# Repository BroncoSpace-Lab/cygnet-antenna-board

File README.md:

# antenna-board

This repo contains the KiCAD files for the PROVES Kit Antenna Board. This board currently goes on the +Z endcap of the satellite and hosts the antennas, interfacing ports, and some other support circuitry!

## antenna_top_cap_board_v1a
This antenna board is a reformat of the V1 Antenna Board that consolidates a bunch of the 2pos Picolock and STEMMA connectors into a single connector that runs back to the V3b EPS Board. We are probably going to leapfrog this version to land on V2 which fundementally changes things about the antenna feed path. 

## antenna_top_cap_v2
This version of the antenna top cap featuers major changes to the antenna feed path and debug passthroughs. Notable features are as follows: 
- Updated Balun Part Number (no longer sucks! still sucks to solder though)
- Addition of 12-pos and 5-pos Battery Board and Flight Controller Board debug connectors.

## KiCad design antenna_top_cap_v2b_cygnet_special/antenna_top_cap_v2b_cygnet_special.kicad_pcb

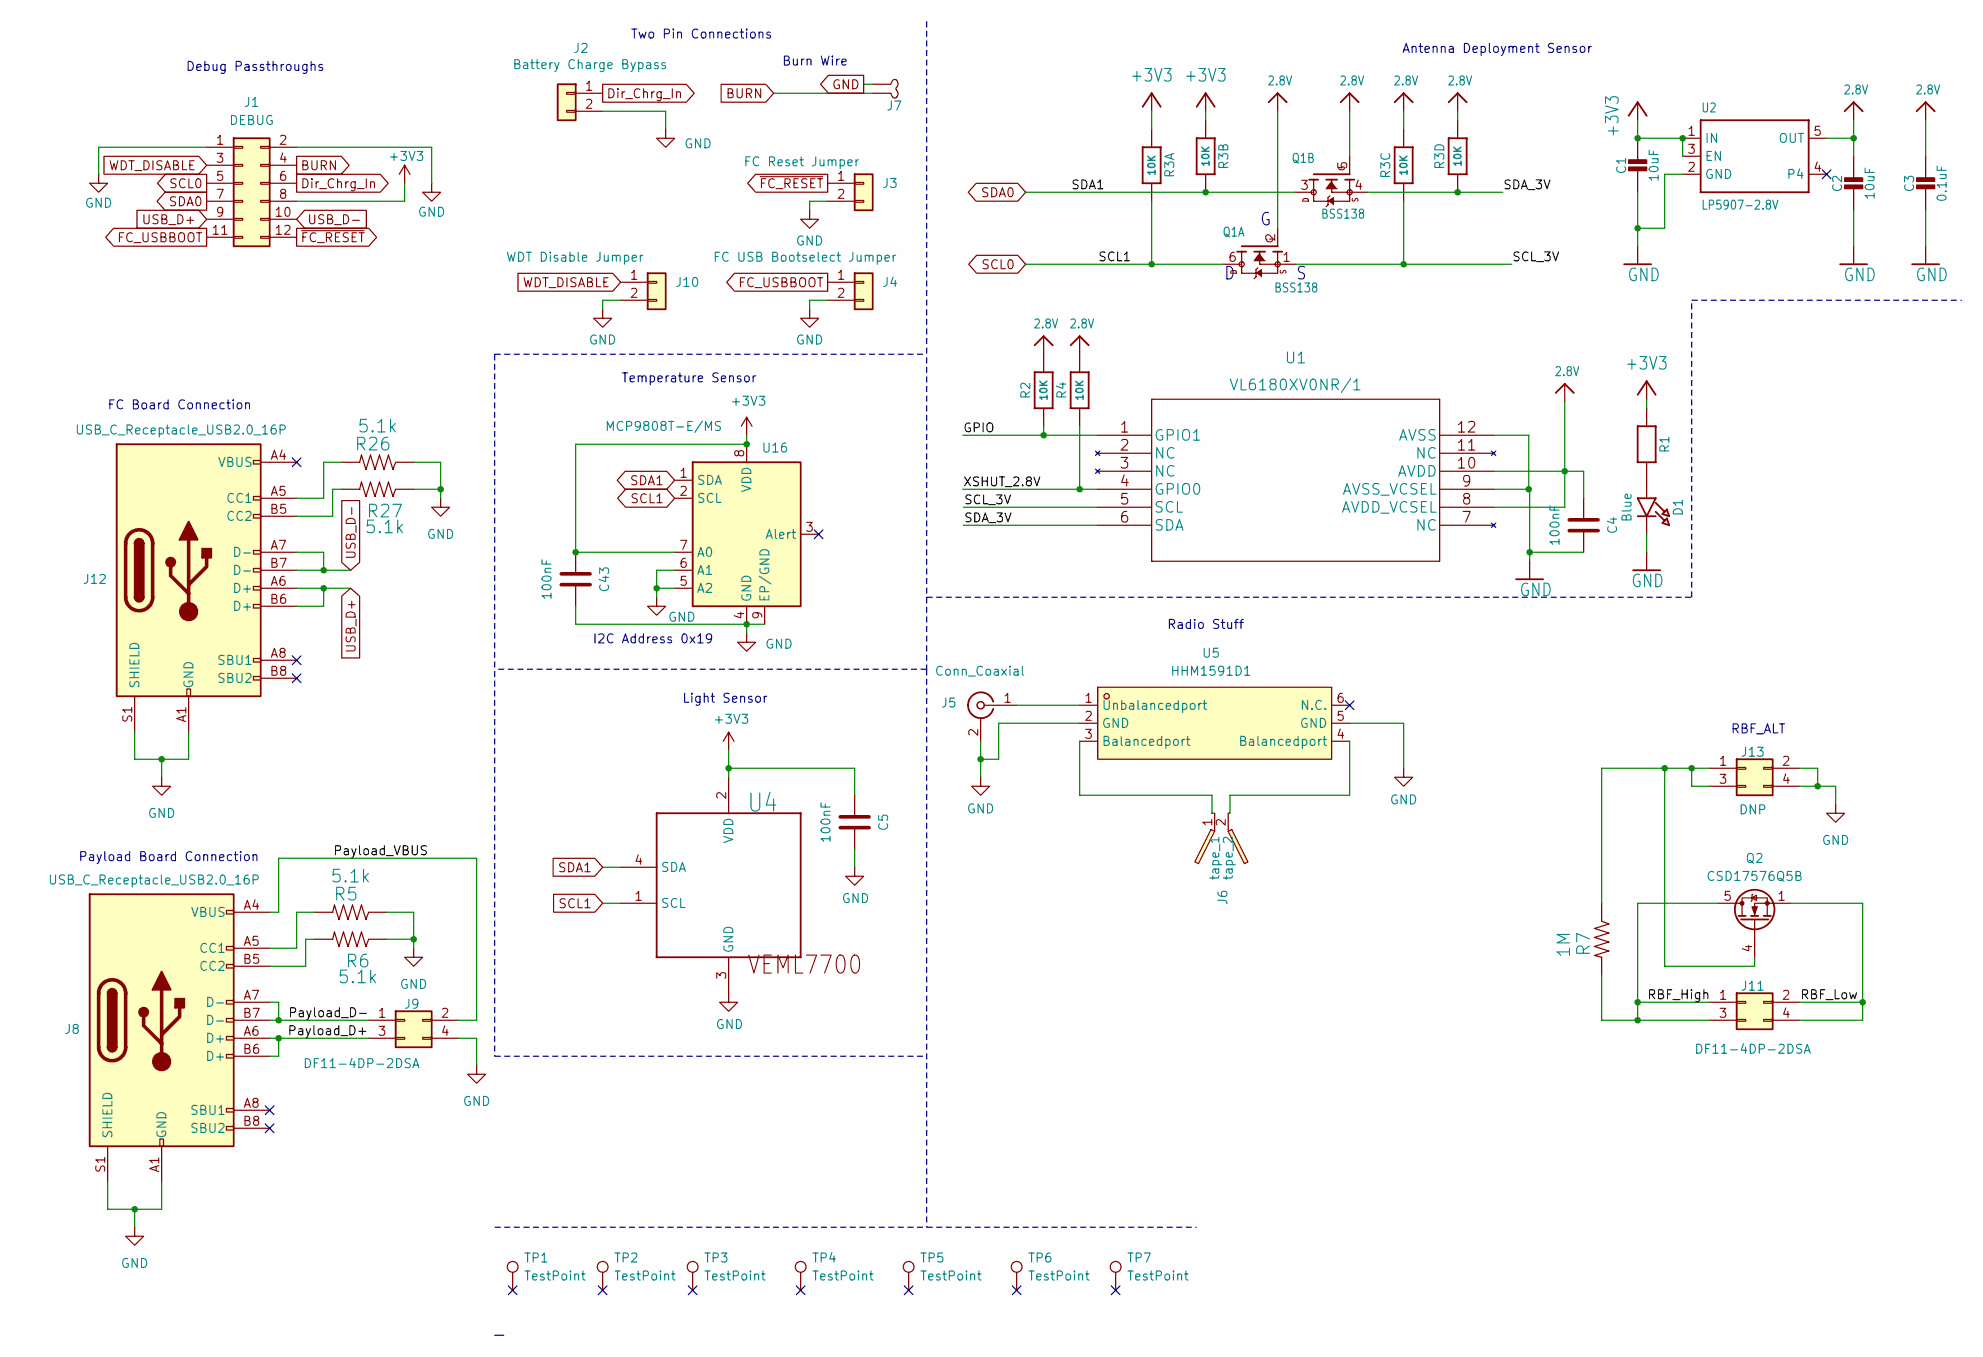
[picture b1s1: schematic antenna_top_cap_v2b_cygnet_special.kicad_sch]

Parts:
C1, C2: 10uF; C_0805_2012Metric
C3: 0.1uF; C_0603_1608Metric
C4, C5, C43: 100nF; C_0805_2012Metric
D1: Blue; LED_0603_1608Metric
J1: DEBUG; Hirose_DF11-12DP-2DSA_2x06_P2.00mm_Vertical
J2: Battery Charge Bypass; PinHeader_1x02_P2.54mm_Vertical
J3: FC Reset Jumper; PinHeader_1x02_P2.54mm_Vertical
J4: FC USB Bootselect Jumper; PinHeader_1x02_P2.54mm_Vertical
J5: Conn_Coaxial; SMA_Amphenol_901-144_Vertical
J6: Tape_Measure_Antenna
J7: Burn_Wire
J8, J12: USB_C_Receptacle_USB2.0_16P; USB_C_Receptacle_HRO_TYPE-C-31-M-12
J9, J11: DF11-4DP-2DSA; Hirose_DF11-4DP-2DSA_2x02_P2.00mm_Vertical
J10: WDT Disable Jumper; PinHeader_1x02_P2.54mm_Vertical
J13: DNP; Hirose_DF11-4DP-2DSA_2x02_P2.00mm_Vertical
Q1: BSS138; SOT-363_SC-70-6
Q2: CSD17576Q5B; TDSON-8-1
R1: 10k; R_0402_1005Metric
R2, R4: 10K; R_0603_1608Metric
R3: 10K; R_Array_Convex_4x0603
R5, R6, R26, R27: 5.1k; R_0603_1608Metric
R7: 1M; R_0603_1608Metric
TP1, TP2, TP3, TP4, TP5, TP6, TP7: TestPoint; MountingHole_2.7mm_M2.5_Pad
U1: VL6180XV0NR/1; VL6180
U2: LP5907-2.8V; SOT-23-5
U4: VEML7700; XDCR_VEML7700-TT
U5: HHM1591D1; XFMR-SMD_HHM1591D1; LCSC Part C74209
U16: MCP9808T-E/MS; MSOP-8-1EP_3x3mm_P0.65mm_EP1.5x1.8mm_ThermalVias

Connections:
2.8V: C2.1, C3.1, C4.1, Q1.2 (G), Q1.5 (G), R2.2, R3.3 (1), R3.4 (1), R4.2, U1.8 (AVDD_VCSEL), U1.10 (AVDD), U2.5 (OUT)
+3V3: C1.1, C5.1, C43.1, J1.8, R1.1, R3.1, R3.2 (1), U2.1 (IN), U2.3 (EN), U4.2 (VDD), U16.7 (A0), U16.8 (VDD)
/GPIO: R2.1, U1.1 (GPIO1)
/Payload_D+: J8.A6 (D+), J8.B6 (D+), J9.3
/Payload_D-: J8.A7 (D-), J8.B7 (D-), J9.1
/Payload_VBUS: J8.A4 (VBUS), J8.A9 (VBUS), J8.B4 (VBUS), J8.B9 (VBUS), J9.2
/RBF_High: J11.1, J11.3, Q2.5 (D), R7.2
/RBF_Low: J11.2, J11.4, Q2.1 (S), Q2.2 (S), Q2.3 (S)
/SCL_3V: Q1.1 (S), R3.6 (2), U1.5 (SCL)
/SDA_3V: Q1.4 (S), R3.5 (2), U1.6 (SDA)
/XSHUT_2.8V: R4.1, U1.4 (GPIO0)
BURN: J1.4, J7.1 (Power)
Dir_Chrg_In: J1.6, J2.1
FC_USBBOOT: J1.11, J4.1
GND: C1.2, C2.2, C3.2, C4.2, C5.2, C43.2, D1.2 (C), J1.1, J1.2, J2.2, J3.2, J4.2, J5.2 (Ext), J7.2 (GND), J8.A1 (GND), J8.A12 (GND), J8.B1 (GND), J8.B12 (GND), J8.S1 (SHIELD), J9.4, J10.2, J12.A1 (GND), J12.A12 (GND), J12.B1 (GND), J12.B12 (GND), J12.S1 (SHIELD), J13.2, J13.4, R5.1, R6.1, R26.1, R27.1, U1.9 (AVSS_VCSEL), U1.12 (AVSS), U2.2 (GND), U4.3 (GND), U5.2 (GND), U5.5 (GND), U16.4 (GND), U16.5 (A2), U16.6 (A1), U16.9 (EP/GND)
unnamed: D1.1 (A), R1.2
unnamed: J5.1 (In), U5.1 (Unbalancedport)
unnamed: J6.1 (tape), U5.3 (Balancedport)
unnamed: J6.2 (tape), U5.4 (Balancedport)
unnamed: J8.A5 (CC1), R5.2
unnamed: J8.B5 (CC2), R6.2
unnamed: J12.A5 (CC1), R26.2
unnamed: J12.B5 (CC2), R27.2
unnamed: J13.1, J13.3, Q2.4 (G), R7.1
SCL0: J1.5, Q1.6 (D), R3.8 (2), U4.1 (SCL), U16.2 (SCL)
SDA0: J1.7, Q1.3 (D), R3.7 (2), U4.4 (SDA), U16.1 (SDA)
USB_D+: J1.9, J12.A6 (D+), J12.B6 (D+)
USB_D-: J1.10, J12.A7 (D-), J12.B7 (D-)
WDT_DISABLE: J1.3, J10.1
~FC_RESET: J1.12, J3.1

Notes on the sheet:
Light Sensor
Two Pin Connections
I2C Address 0x19
Antenna Deployment Sensor
Radio Stuff
Debug Passthroughs
FC Board Connection
RBF_ALT
Payload Board Connection
Burn Wire
Temperature Sensor

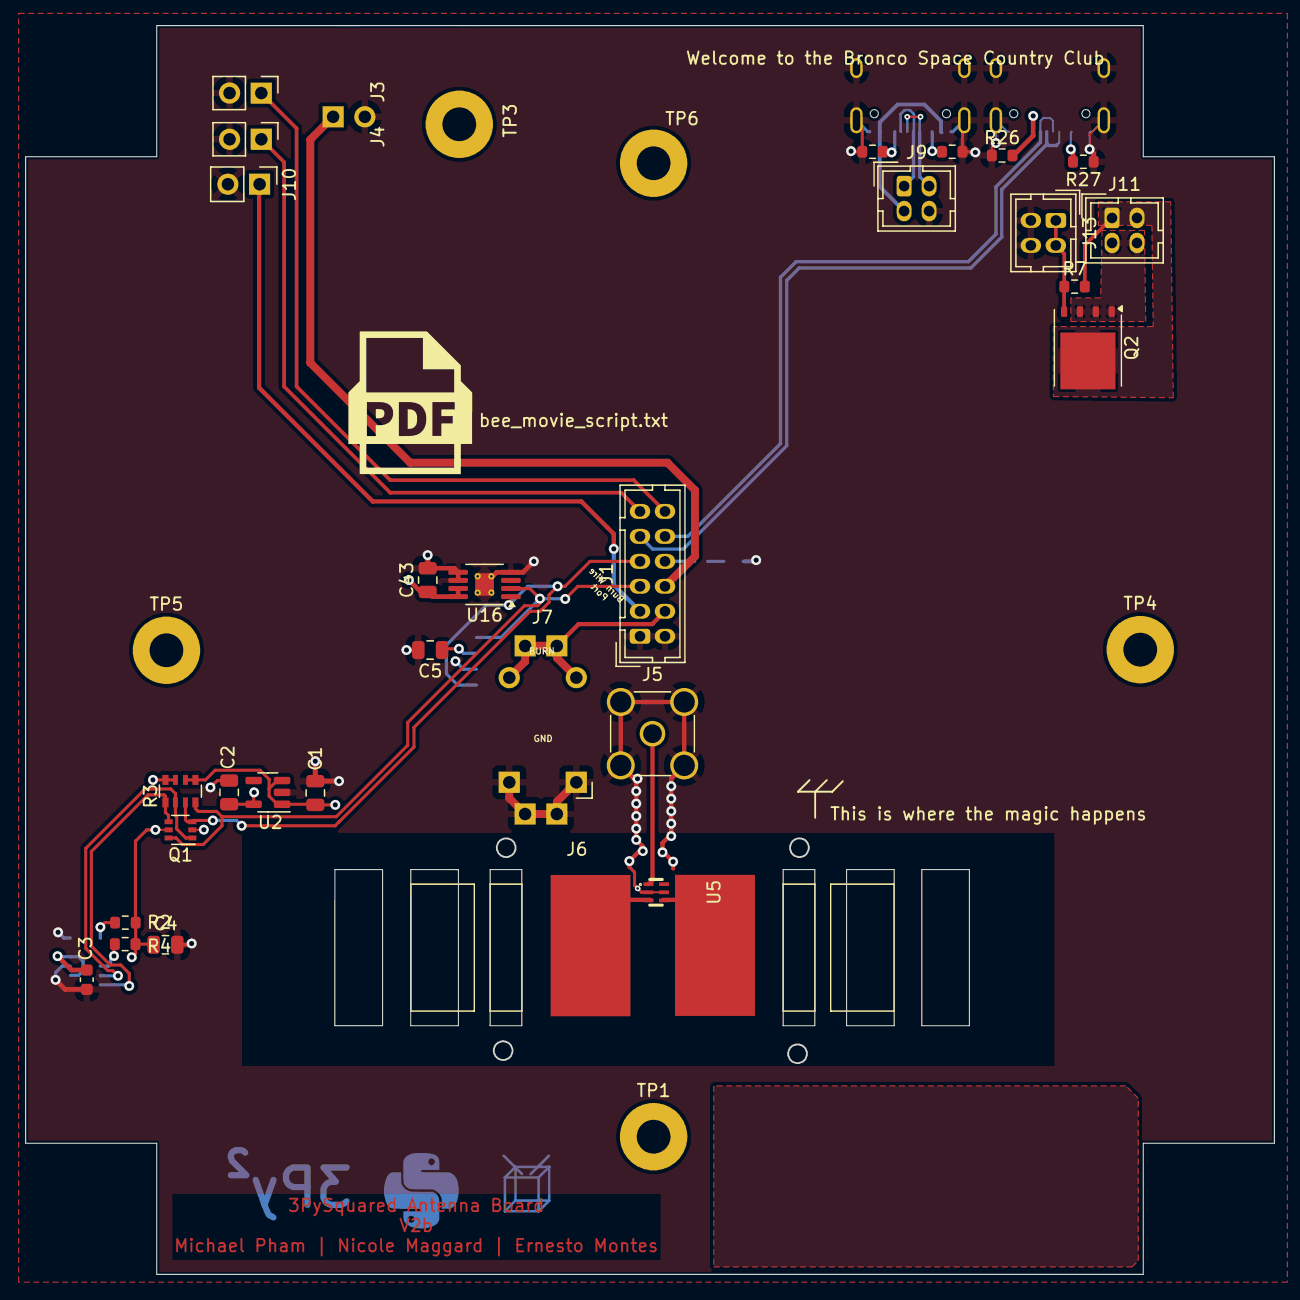
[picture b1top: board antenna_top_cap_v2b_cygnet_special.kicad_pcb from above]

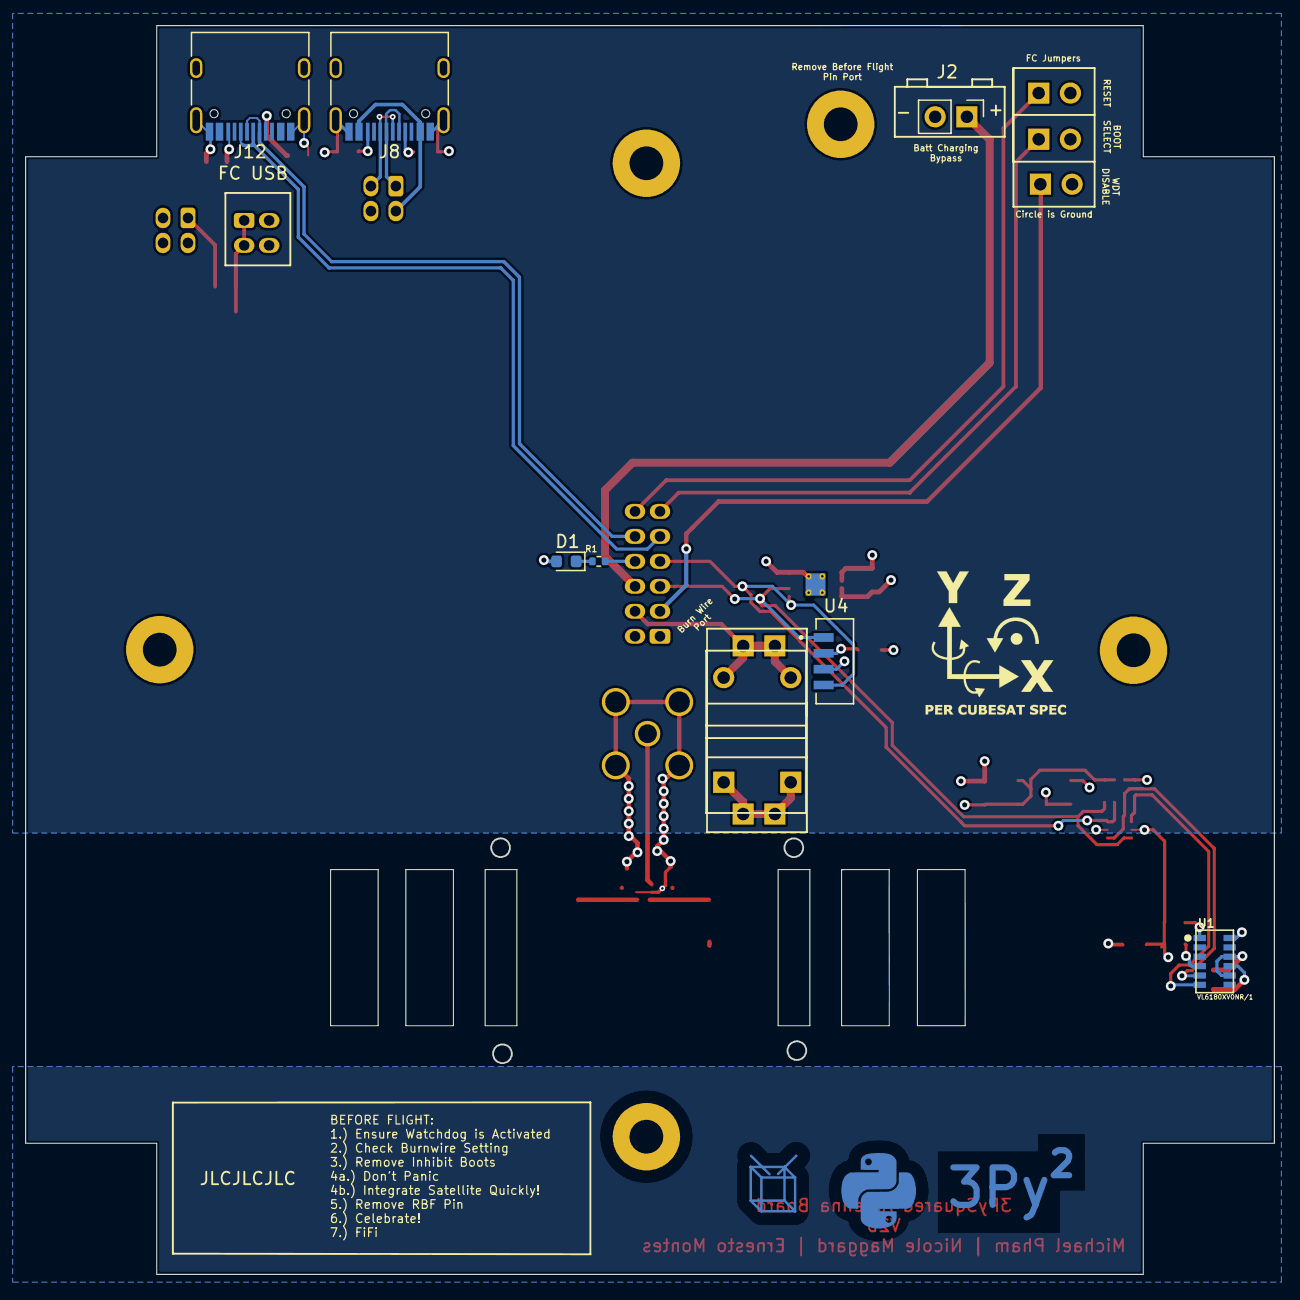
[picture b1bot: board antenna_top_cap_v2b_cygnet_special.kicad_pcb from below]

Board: 2 copper layers, 100.0 x 100.0 mm, 41 parts (7 on the bottom side), 30 nets.

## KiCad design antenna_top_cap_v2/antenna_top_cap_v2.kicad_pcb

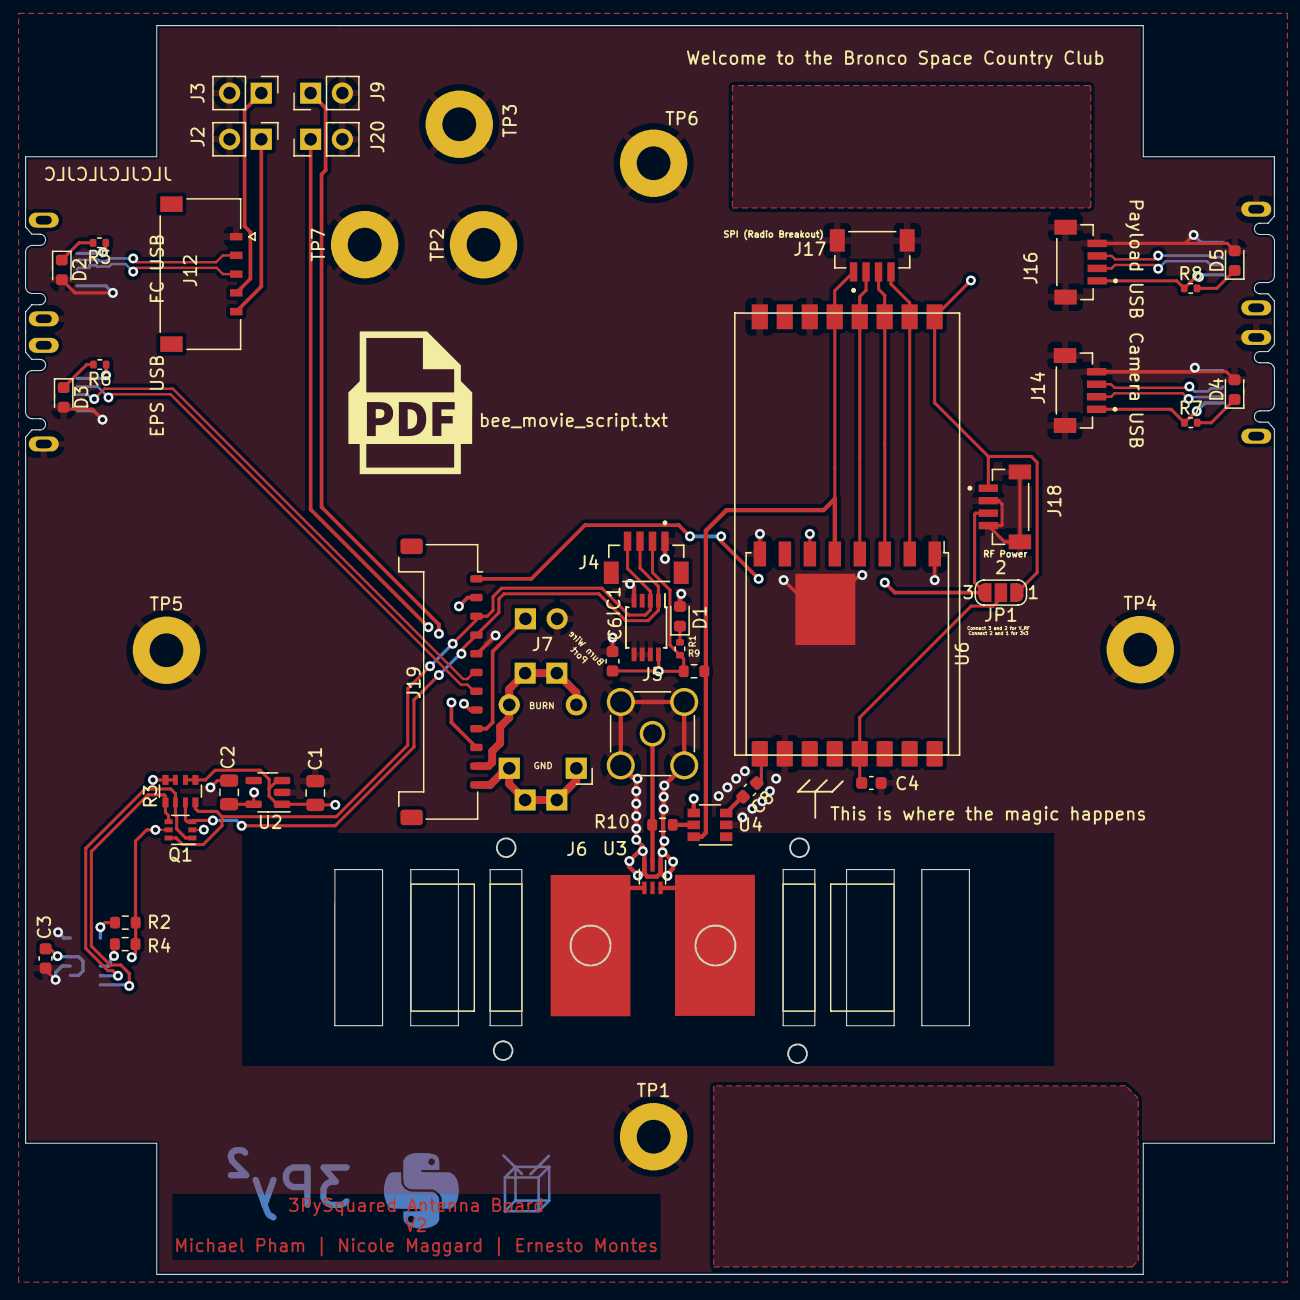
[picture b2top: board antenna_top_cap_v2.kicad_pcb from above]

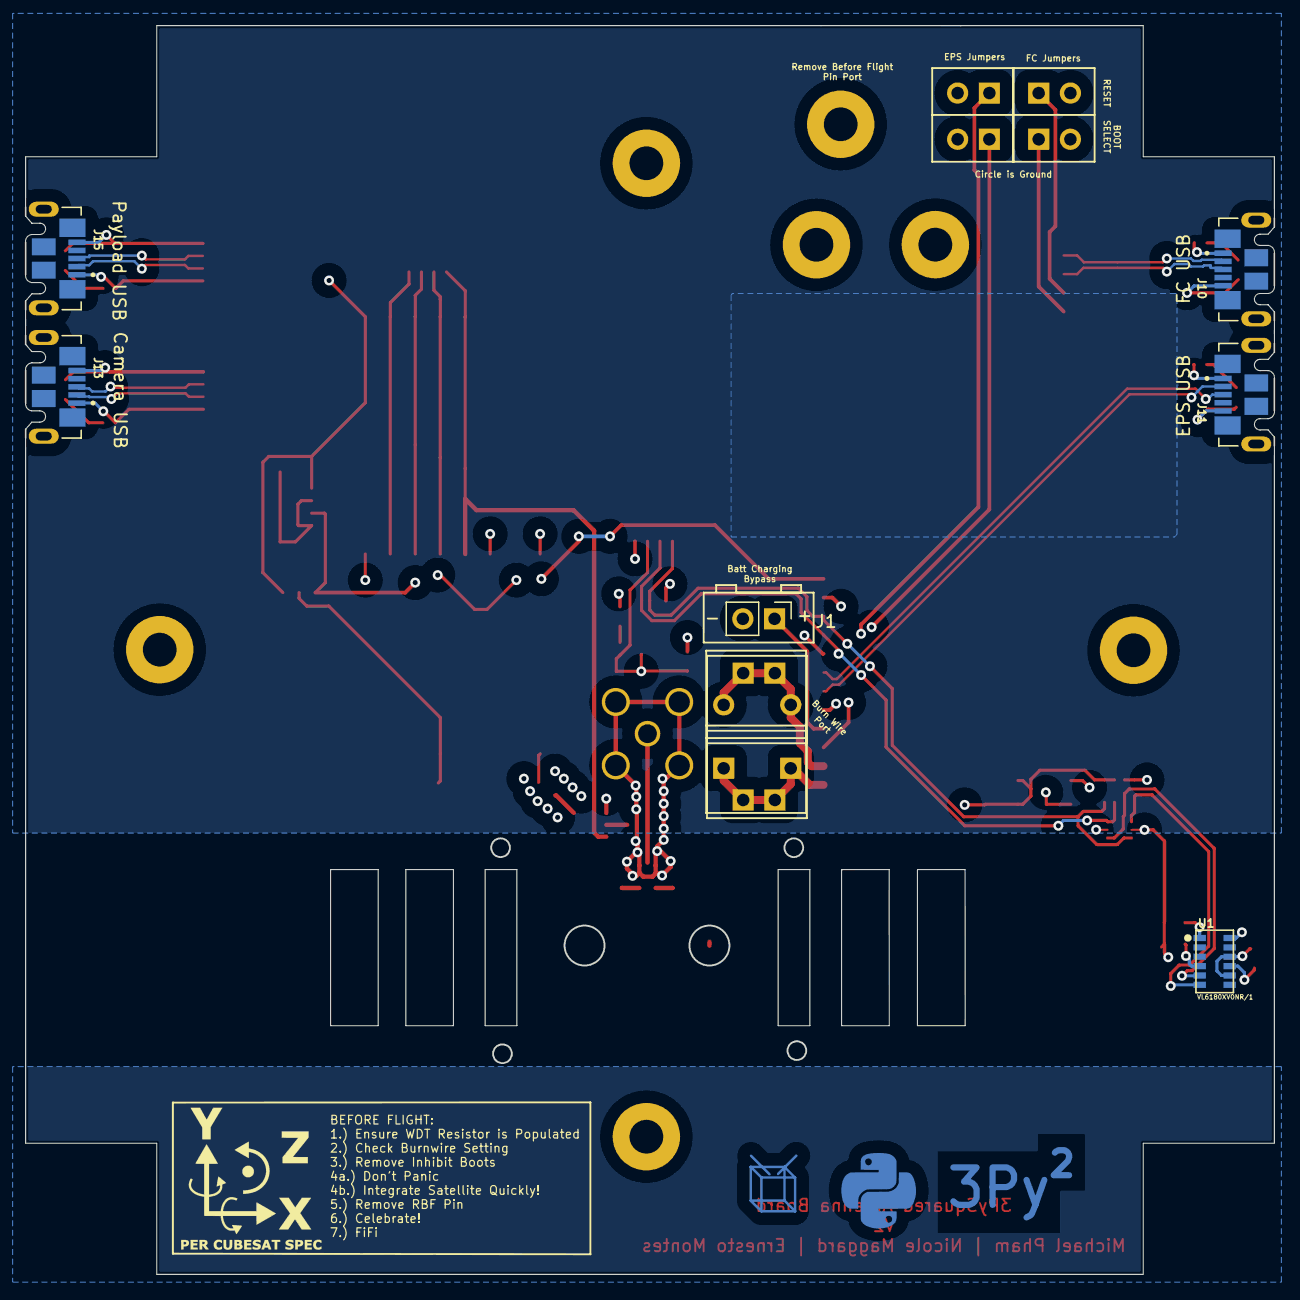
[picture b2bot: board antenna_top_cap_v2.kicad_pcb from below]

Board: 4 copper layers, 100.0 x 100.0 mm, 56 parts (6 on the bottom side), 45 nets.

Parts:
C1, C2: 10uF; C_0805_2012Metric
C3: 0.1uF; C_0603_1608Metric
C4: 10uF; C_0603_1608Metric
C6: 100nf; C_0603_1608Metric
C8: 100pf; C_0603_1608Metric
D1, D2, D3, D4, D5: Blue; LED_0603_1608Metric
IC1: PCT2075DP,118; TSSOP-8_3x3mm_P0.65mm
J1: Battery Charge Bypass; PinHeader_1x02_P2.54mm_Vertical
J2: EPS USB Bootselect Jumper; PinHeader_1x02_P2.54mm_Vertical
J3: EPS Reset Jumper; PinHeader_1x02_P2.54mm_Vertical
J4, J14, J16, J17, J18: BM04B-SRSS-TB(LF)(SN); JST_BM04B-SRSS-TB(LF)(SN)
J5: Conn_Coaxial; SMA_Amphenol_901-144_Vertical
J6: Tape_Measure_Antenna
J7: Burn_Wire
J9: FC Reset Jumper; PinHeader_1x02_P2.54mm_Vertical
J10: USB_B_Micro_FC; MOLEX_105164-0001(round)
J11: USB_B_Micro_EPS; MOLEX_105164-0001(round)
J12: FC Board Connector; MOLEX_5040500591
J13, J15: USB_B_Micro; MOLEX_105164-0001(round)
J19: EPS Board Connector; Molex_Pico-Lock_504050-1291_1x12-1MP_P1.50mm_Horizontal
J20: FC USB Bootselect Jumper; PinHeader_1x02_P2.54mm_Vertical
JP1: SolderJumper_3_Open; SolderJumper-3_P1.3mm_Open_RoundedPad1.0x1.5mm_NumberLabels
Q1: BSS138; SOT-363_SC-70-6
R1, R5, R6, R7, R8: 1K; R_0402_1005Metric
R2, R4: 10K; R_0603_1608Metric
R3: 10K; R_Array_Convex_4x0603
R9: 10k; R_0603_1608Metric
R10: DNI; R_0603_1608Metric
TP1, TP2, TP3, TP4, TP5, TP6, TP7: TestPoint; MountingHole_2.7mm_M2.5_Pad
U1: VL6180XV0NR/1; VL6180
U2: LP5907-2.8V; SOT-23-5
U3: NCS1.5-232+; Balun_Johanson_0896BM15A0001
U4: AS193-73LF; SuperSOT-6
U5: RFM98PW
U6: RFM9xBreakout; HOPERF_RFM95W_SMD

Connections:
2.8V: C2.1, C3.1, Q1.2 (G), Q1.5 (G), R2.2, R3.3 (1), R3.4 (1), R4.2, U1.8 (AVDD_VCSEL), U1.10 (AVDD), U2.5 (OUT)
+3V3: C1.1, C6.1, IC1.8 (VCC), J4.2, J18.1, J19.2, JP1.1 (A), R1.1, R3.1, R3.2 (1), R9.1, U2.1 (IN), U2.3 (EN), U4.4 (V2), U5.9 (3.3V), U6.6 (~RESET)
/2d+: J13.3 (D+), J14.3
/2d-: J13.2 (D-), J14.2
/3d+: J15.3 (D+), J16.3
/3d-: J15.2 (D-), J16.2
/GPIO: R2.1, U1.1 (GPIO1)
/SCL_3V: Q1.1 (S), R3.6 (2), U1.5 (SCL)
/SDA_3V: Q1.4 (S), R3.5 (2), U1.6 (SDA)
/XSHUT_2.8V: R4.1, U1.4 (GPIO0)
BURN: J7.1 (Power), J19.11
BURN_GND: J7.2 (GND), J19.12
Balun: R10.1, U4.5 (output)
Dir_Chrg_In: J1.1, J19.9
EPS_USBBOOT: J2.1, J19.10
EPS_USB_D+: J11.3 (D+), J19.6
EPS_USB_D-: J11.2 (D-), J19.7
FC_USBBOOT: J12.5, J20.1
FC_USB_D+: J10.3 (D+), J12.3
FC_USB_D-: J10.2 (D-), J12.2
GND: C1.2, C2.2, C3.2, C4.1, C6.2, D1.2 (C), D2.2 (C), D3.2 (C), D4.2 (C), D5.2 (C), IC1.4 (GND), IC1.5 (A2), IC1.6 (A1), IC1.7 (A0), J1.2, J2.2, J3.2, J4.1, J5.2 (Ext), J9.2, J10.5 (GND), J10.SH1 (Shield), J11.5 (GND), J11.SH1 (Shield), J12.1, J13.5 (GND), J13.SH1 (Shield), J14.4, J14.S1 (SHIELD), J14.S2 (SHIELD), J15.5 (GND), J15.SH1 (Shield), J16.4, J16.S1 (SHIELD), J16.S2 (SHIELD), J17.S1 (SHIELD), J17.S2 (SHIELD), J18.2, J18.4, J18.S1 (SHIELD), J18.S2 (SHIELD), J19.5, J20.2, TP1.1, TP2.1, TP3.1, TP4.1, TP5.1, TP6.1, TP7.1, U1.9 (AVSS_VCSEL), U1.12 (AVSS), U2.2 (GND), U3.1 (GND), U3.3 (GND), U4.2 (GND), U5.2 (GND), U5.14 (RESET), U5.16 (GND), U5.17 (GND), U6.1 (GND), U6.8 (GND), U6.10 (GND)
unnamed: D1.1 (A), R1.2
unnamed: D2.1 (A), R5.2
unnamed: D3.1 (A), R6.2
unnamed: D4.1 (A), R7.2
unnamed: D5.1 (A), R8.2
unnamed: J5.1 (In), R10.2, U3.2
unnamed: J6.1 (tape), U3.4
unnamed: J6.2 (tape), U3.6
unnamed: J10.1 (VBUS), R5.1
unnamed: J11.1 (VBUS), R6.1
unnamed: J13.1 (VBUS), J14.1, R7.1
unnamed: J15.1 (VBUS), J16.1, R8.1
unnamed: C8.2, U4.3 (input2)
OUT2: C8.1, U5.1 (ANT), U6.9 (ANT)
RF_VCC: C4.2, JP1.2 (C), U5.5 (VCC), U6.13 (3V3)
SCL1: IC1.2 (SCL), J4.4, J19.3, Q1.6 (D), R3.8 (2)
SDA1: IC1.1 (SDA), J4.3, J19.4, Q1.3 (D), R3.7 (2)
SPI0_CS0: J17.1, R9.2, U4.6 (V1), U5.13 (NSS), U6.5 (CS)
SPI0_MISO: J17.4, U5.10 (MISO), U6.2 (MISO)
SPI0_MOSI: J17.3, U5.11 (MOSI), U6.3 (MOSI)
SPI0_SCK: J17.2, U5.12 (SCK), U6.4 (SCK)
V_RF: J18.3, J19.1, JP1.3 (B)
~EPS_RESET: J3.1, J19.8
~FC_RESET: J9.1, J12.4

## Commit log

2024-05-29 Added GitIgnore
2024-06-08 Updated gitignore
2024-06-13 Started wiring with 12-pos connector for V3b
2024-06-15 Scooted IC Layout
2024-06-17 Update antenna_top_cap.kicad_pcb
    Connected Direct Change to the 12 Pin Picolock
2024-06-17 Connected USB Breakout
2024-06-17 Finished Connecting 12Pos Connections
2024-06-17 Addressed all DRC Errors
2024-06-17 Added Jumper to Aux RF Line
    Added an 0603 Jumper to break the Aux RF connection when not in use
2024-06-18 Relocated RF SPI Breakout
2024-06-18 Removed redundant trace
    For some reason there was both a 2.8V trace on the F.Cu and the B.Cu layers. Might be an artifact of the original design. The trace on the B.Cu layer was removed
2024-06-18 Updated Solder Mask
2024-06-18 Created V2 Antenna Board
2024-06-19 Schematic Updates and Renaming a Bunch of Files
2024-06-19 Un-nested files
2024-06-19 Swapped Balun
    New Balun Part Number!
    Minicircuits: NCS1.5-232+
    Schematic and PCB Layout Updated
2024-06-19 Added Schematic Symbols for FC Debug Port
2024-06-20 SDA / SCL Hotfix
    See this issue: https://github.com/proveskit/antenna-board/issues/6
2024-06-20 Removed J8 (I2C Breakout)
2024-06-20 Lock File Stuff
2024-06-20 fixed the schematic
    cool beans
2024-06-23 Removed One of the I2C Breakouts
2024-06-23 Added mounting hole keep out areas
2024-06-23 Completed LiDAR Layout
2024-06-24 Finished On Board Placements
2024-06-24 Completed Layout
2024-06-24 Completed DRC Reviews
2024-06-24 As Ordered June 23, 2023
2024-06-24 Updated BOM
2024-08-19 Released Lock
2025-04-15 Created V2a Project
2025-04-16 Deleted Unused Parts
2025-04-16 Added USB and DF11 Debug Connector
2025-04-16 Added MCP Temperature Sensor
2025-04-17 Added VEML7700 Light Sensor
2025-04-18 Production Files as Ordered 4/17/2025
2025-05-03 Corrected BOM Error
    The 5.1K USB-C Resistors were not populated by accident on the first production run.
2025-07-16 Updated Impedance of USB Traces
2025-07-16 Added Payload USB Passthrough
2025-07-30 Redid USB Trace Impedance
2025-07-31 Added Alt RBF
2025-08-04 Initial Board
2025-08-04 As Ordered Aug 4 2025
